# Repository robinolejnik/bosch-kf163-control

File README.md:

# bosch-kf163-control
Replacement PLL/TGA PCB to control Bosch KF83/KF163/KF453/KF165 radios

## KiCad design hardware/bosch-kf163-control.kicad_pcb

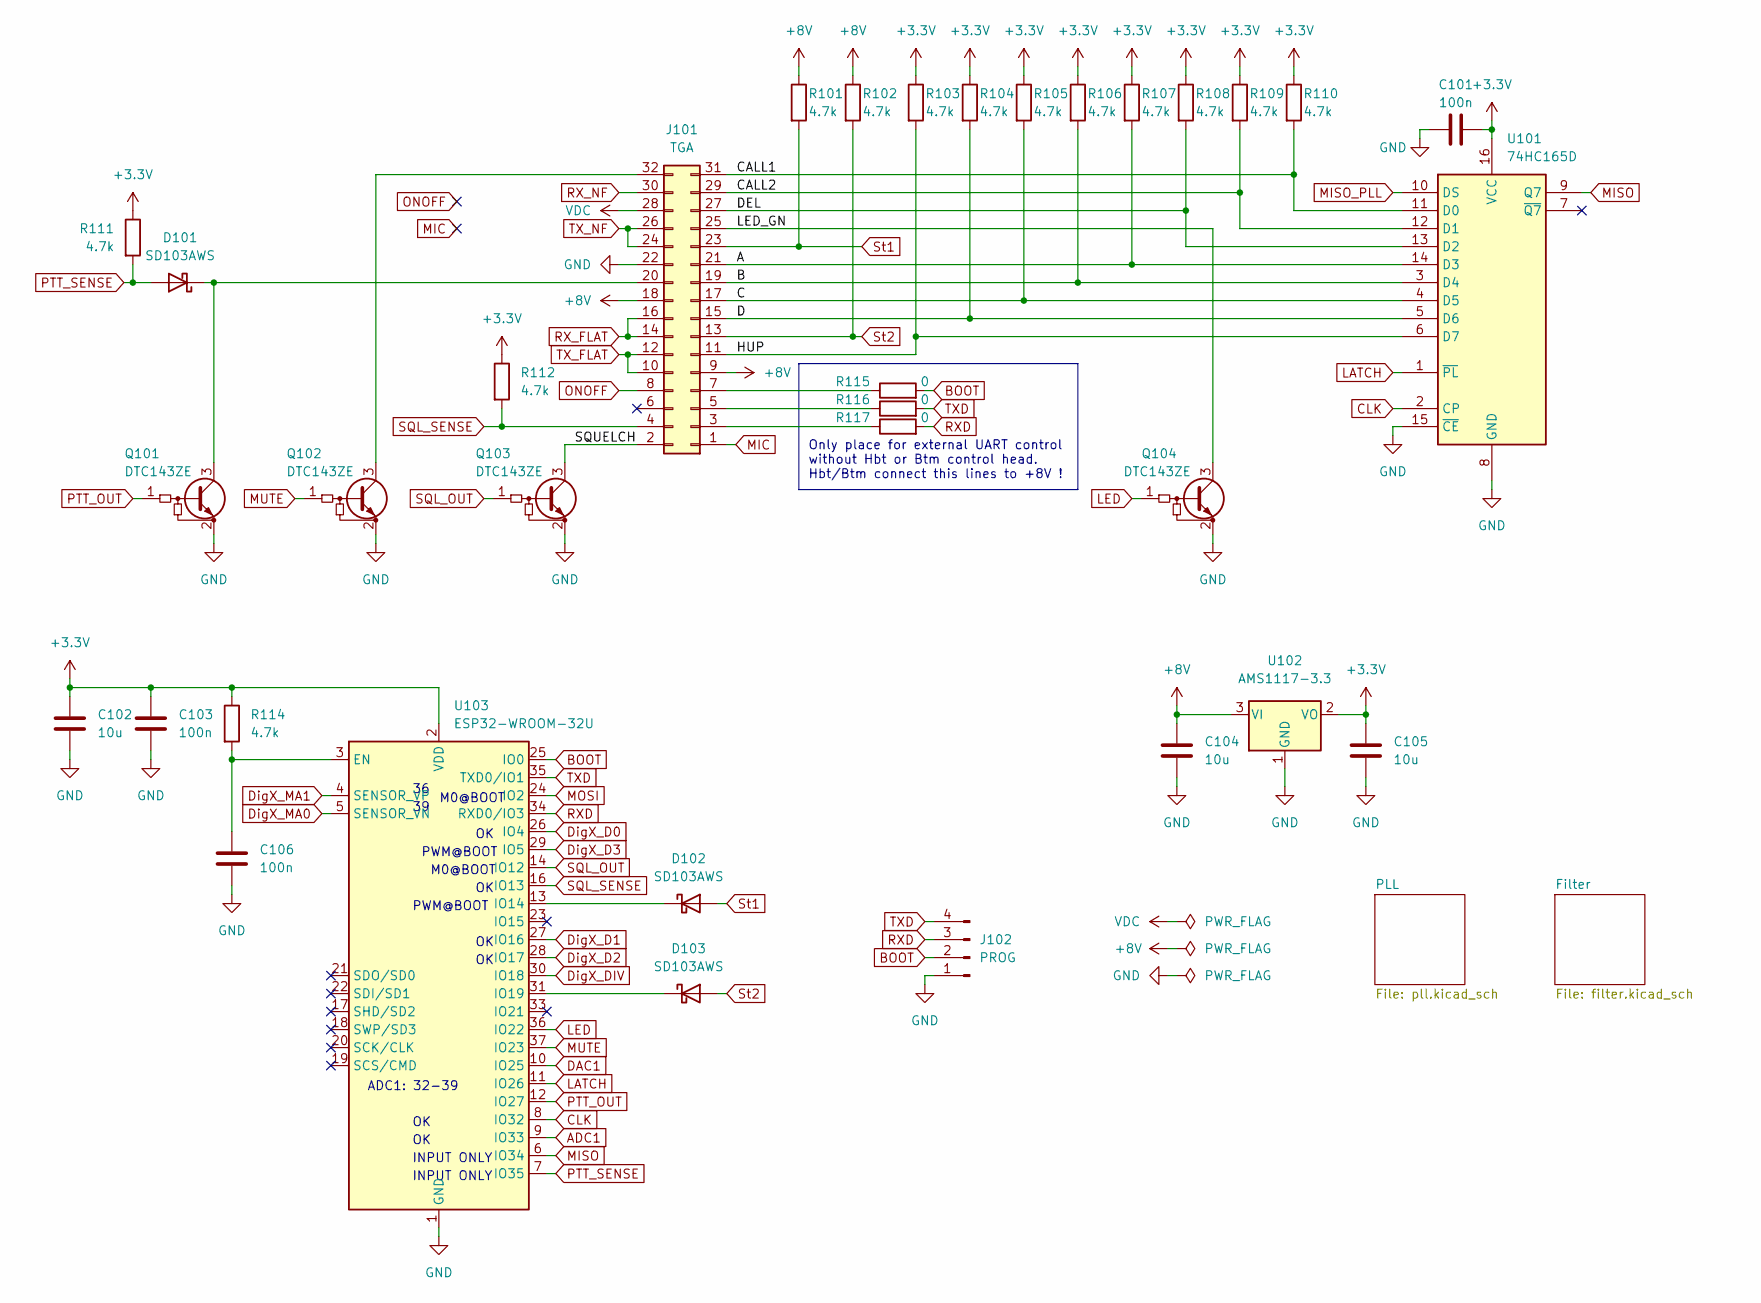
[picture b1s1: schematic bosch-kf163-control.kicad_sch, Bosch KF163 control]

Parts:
C101, C103, C106: 100n; C_0603_1608Metric; LCSC C14663
C102, C104, C105: 10u; C_0603_1608Metric; LCSC C2922482
D101, D102, D103: SD103AWS; D_SOD-323; LCSC C438010
J101: TGA; PinSocket_2x16_P2.54mm_Vertical; LCSC C115248
J102: PROG; PinHeader_1x04_P2.54mm_Vertical
Q101, Q102, Q103, Q104: DTC143ZE; SOT-523; LCSC C248787
R101, R102, R103, R104, R105, R106, R107, R108, R109, R110, R111, R112, R114: 4.7k; R_0603_1608Metric; LCSC C105428
R115, R116, R117: 0; R_0603_1608Metric; LCSC C100044
U101: 74HC165D; SOIC-16_3.9x9.9mm_P1.27mm; LCSC C5613
U102: AMS1117-3.3; SOT-223-3_TabPin2; LCSC C173386
U103: ESP32-WROOM-32U; LCSC C328062

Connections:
+3V3: C101.2, C102.1, C103.1, C105.1, R103.1, R104.1, R105.1, R106.1, R107.1, R108.1, R109.1, R110.1, R111.1, R112.1, R114.1, U101.16 (VCC), U102.2 (VO), U103.2 (VDD); also elsewhere on the board
+8V: C104.1, J101.9, J101.18, R101.1, R102.1, U102.3 (VI)
/A: J101.21, R107.2, U101.14 (D3)
/B: J101.19, R106.2, U101.3 (D4)
/C: J101.17, R105.2, U101.4 (D5)
/CALL1: J101.31, R110.2, U101.11 (D0)
/CALL2: J101.29, R109.2, U101.12 (D1)
/D: J101.15, R104.2, U101.5 (D6)
/DEL: J101.27, R108.2, U101.13 (D2)
/HUP: J101.11, R103.2, U101.6 (D7)
/LED_GN: J101.25, Q104.3 (C)
/SQUELCH: J101.2, Q103.3 (C)
ADC1: U103.9 (IO33); also elsewhere on the board
BOOT: J102.2, R115.2, U103.25 (IO0)
CLK: U101.2 (CP), U103.8 (IO32); also elsewhere on the board
DAC1: U103.10 (IO25); also elsewhere on the board
DigX_D0: U103.26 (IO4); also elsewhere on the board
DigX_D1: U103.27 (IO16); also elsewhere on the board
DigX_D2: U103.28 (IO17); also elsewhere on the board
DigX_D3: U103.29 (IO5); also elsewhere on the board
DigX_DIV: U103.30 (IO18); also elsewhere on the board
DigX_MA0: U103.5 (SENSOR_VN); also elsewhere on the board
DigX_MA1: U103.4 (SENSOR_VP); also elsewhere on the board
GND: C101.1, C102.2, C103.2, C104.2, C105.2, C106.2, J101.22, J102.1, Q101.2 (E), Q102.2 (E), Q103.2 (E), Q104.2 (E), U101.8 (GND), U101.15 (~CE), U102.1 (GND), U103.1 (GND), U103.15 (GND), U103.38 (GND), U103.39 (GND); also elsewhere on the board
LATCH: U101.1 (~PL), U103.11 (IO26); also elsewhere on the board
LED: Q104.1 (B), U103.36 (IO22)
MIC: J101.1
MISO: U101.9 (Q7), U103.6 (IO34)
MISO_PLL: U101.10 (DS); also elsewhere on the board
MOSI: U103.24 (IO2); also elsewhere on the board
MUTE: Q102.1 (B), U103.37 (IO23)
unnamed: C106.1, R114.2, U103.3 (EN)
unnamed: D101.1 (K), J101.20, Q101.3 (C)
unnamed: D102.1 (K), U103.13 (IO14)
unnamed: D103.1 (K), U103.31 (IO19)
unnamed: J101.3, R117.1
unnamed: J101.5, R116.1
unnamed: J101.7, R115.1
unnamed: J101.32, Q102.3 (C)
ONOFF: J101.8
PTT_OUT: Q101.1 (B), U103.12 (IO27)
PTT_SENSE: D101.2 (A), R111.2, U103.7 (IO35)
RXD: J102.3, R117.2, U103.34 (RXD0/IO3)
RX_FLAT: J101.14, J101.16; also elsewhere on the board
RX_NF: J101.30; also elsewhere on the board
SQL_OUT: Q103.1 (B), U103.14 (IO12)
SQL_SENSE: J101.4, R112.2, U103.16 (IO13)
St1: D102.2 (A), J101.23, R101.2
St2: D103.2 (A), J101.13, R102.2
TXD: J102.4, R116.2, U103.35 (TXD0/IO1)
TX_FLAT: J101.10, J101.12; also elsewhere on the board
TX_NF: J101.24, J101.26; also elsewhere on the board
VDC: J101.28

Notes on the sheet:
ADC1: 32-39
M0@BOOT
INPUT ONLY
PWM@BOOT
Only place for external UART control without Hbt or Btm control head. Hbt/Btm connect this lines to +8V !

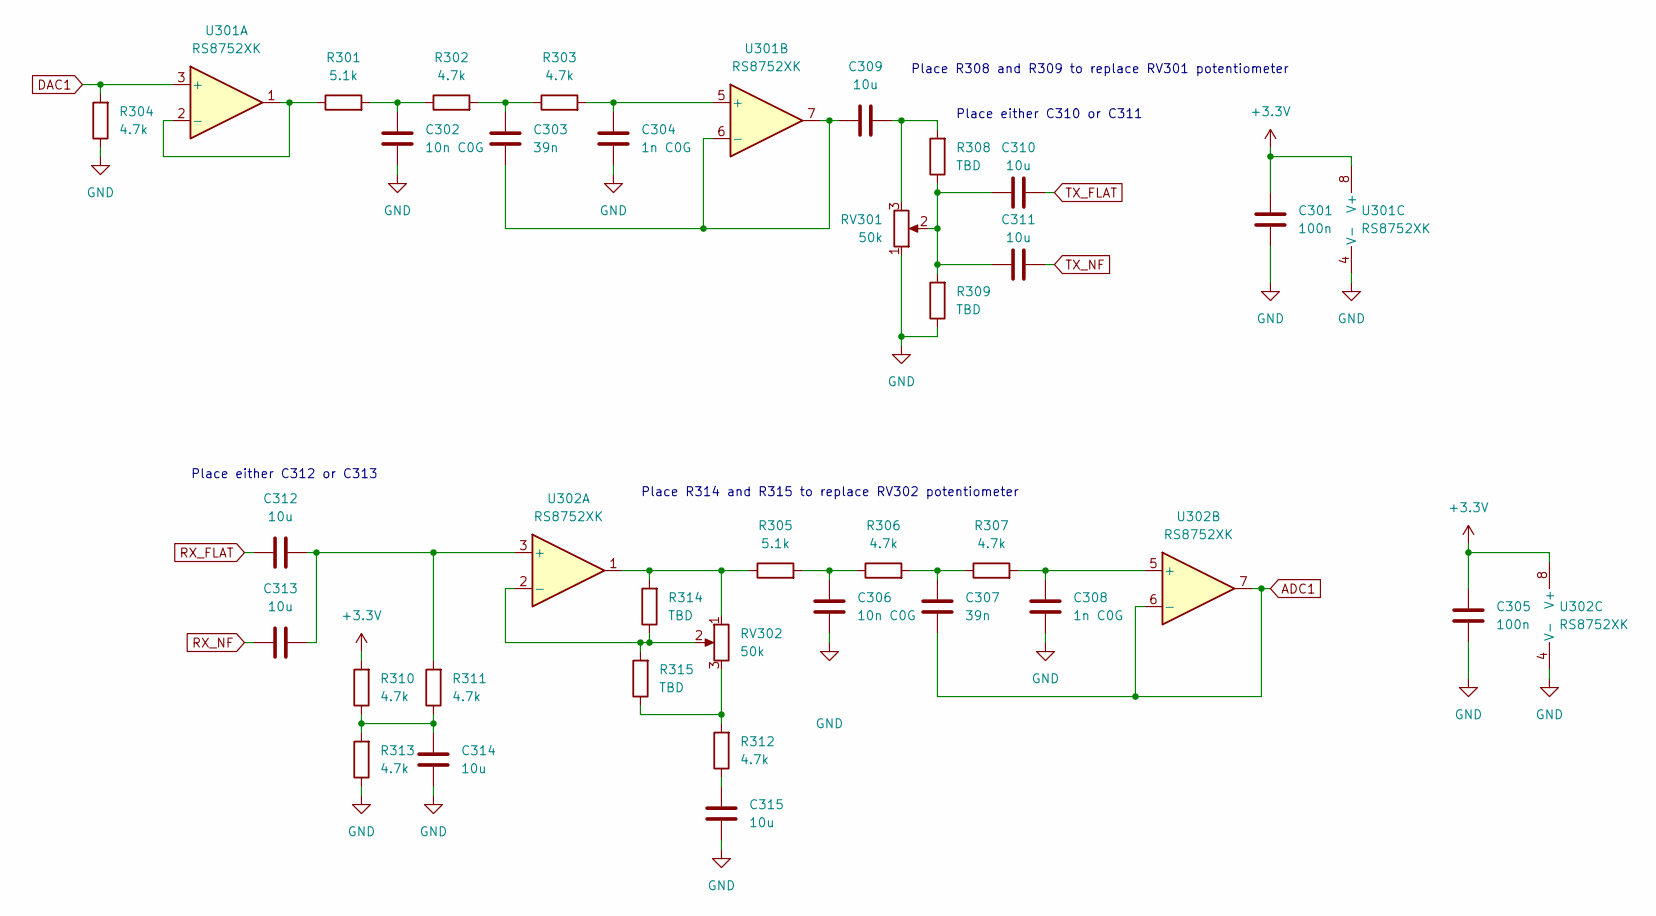
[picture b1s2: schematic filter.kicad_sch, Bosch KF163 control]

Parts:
C301, C305: 100n; C_0603_1608Metric; LCSC C14663
C302, C306: 10n C0G; C_0603_1608Metric; LCSC C389113
C303, C307: 39n; C_0603_1608Metric; LCSC C107091
C304, C308: 1n C0G; C_0603_1608Metric; LCSC C106246
C309, C310, C311, C312, C313, C314, C315: 10u; C_0603_1608Metric; LCSC C2922482
R301, R305: 5.1k; R_0603_1608Metric; LCSC C23186
R302, R303, R304, R306, R307, R310, R311, R312, R313: 4.7k; R_0603_1608Metric; LCSC C105428
R308, R309, R314, R315: TBD; R_0603_1608Metric
RV301, RV302: 50k; Potentiometer_Bourns_TC33X_Vertical; LCSC C145161
U301, U302: RS8752XK; SOIC-8_3.9x4.9mm_P1.27mm; LCSC C236994

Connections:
+3V3: C301.1, C305.1, R310.2, U301.8 (V+), U302.8 (V+); also elsewhere on the board
ADC1: C307.2, U302.6 (-), U302.7; also elsewhere on the board
DAC1: R304.2, U301.3 (+); also elsewhere on the board
GND: C301.2, C302.2, C304.2, C305.2, C306.2, C308.2, C314.2, C315.2, R304.1, R309.1, R313.1, RV301.1, U301.4 (V-), U302.4 (V-); also elsewhere on the board
unnamed: C302.1, R301.2, R302.1
unnamed: C303.1, R302.2, R303.1
unnamed: C303.2, C309.1, U301.6 (-), U301.7
unnamed: C304.1, R303.2, U301.5 (+)
unnamed: C306.1, R305.2, R306.1
unnamed: C307.1, R306.2, R307.1
unnamed: C308.1, R307.2, U302.5 (+)
unnamed: C309.2, R308.2, RV301.3
unnamed: C310.1, C311.1, R308.1, R309.2, RV301.2
unnamed: C312.2, C313.2, R311.2, U302.3 (+)
unnamed: C314.1, R310.1, R311.1, R313.2
unnamed: C315.1, R312.1
unnamed: R301.1, U301.1, U301.2 (-)
unnamed: R305.1, R314.2, RV302.1, U302.1
unnamed: R312.2, R315.1, RV302.3
unnamed: R314.1, R315.2, RV302.2, U302.2 (-)
RX_FLAT: C312.1; also elsewhere on the board
RX_NF: C313.1; also elsewhere on the board
TX_FLAT: C310.2; also elsewhere on the board
TX_NF: C311.2; also elsewhere on the board

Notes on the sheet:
Place R308 and R309 to replace RV301 potentiometer
Place either C310 or C311
Place R314 and R315 to replace RV302 potentiometer
Place either C312 or C313

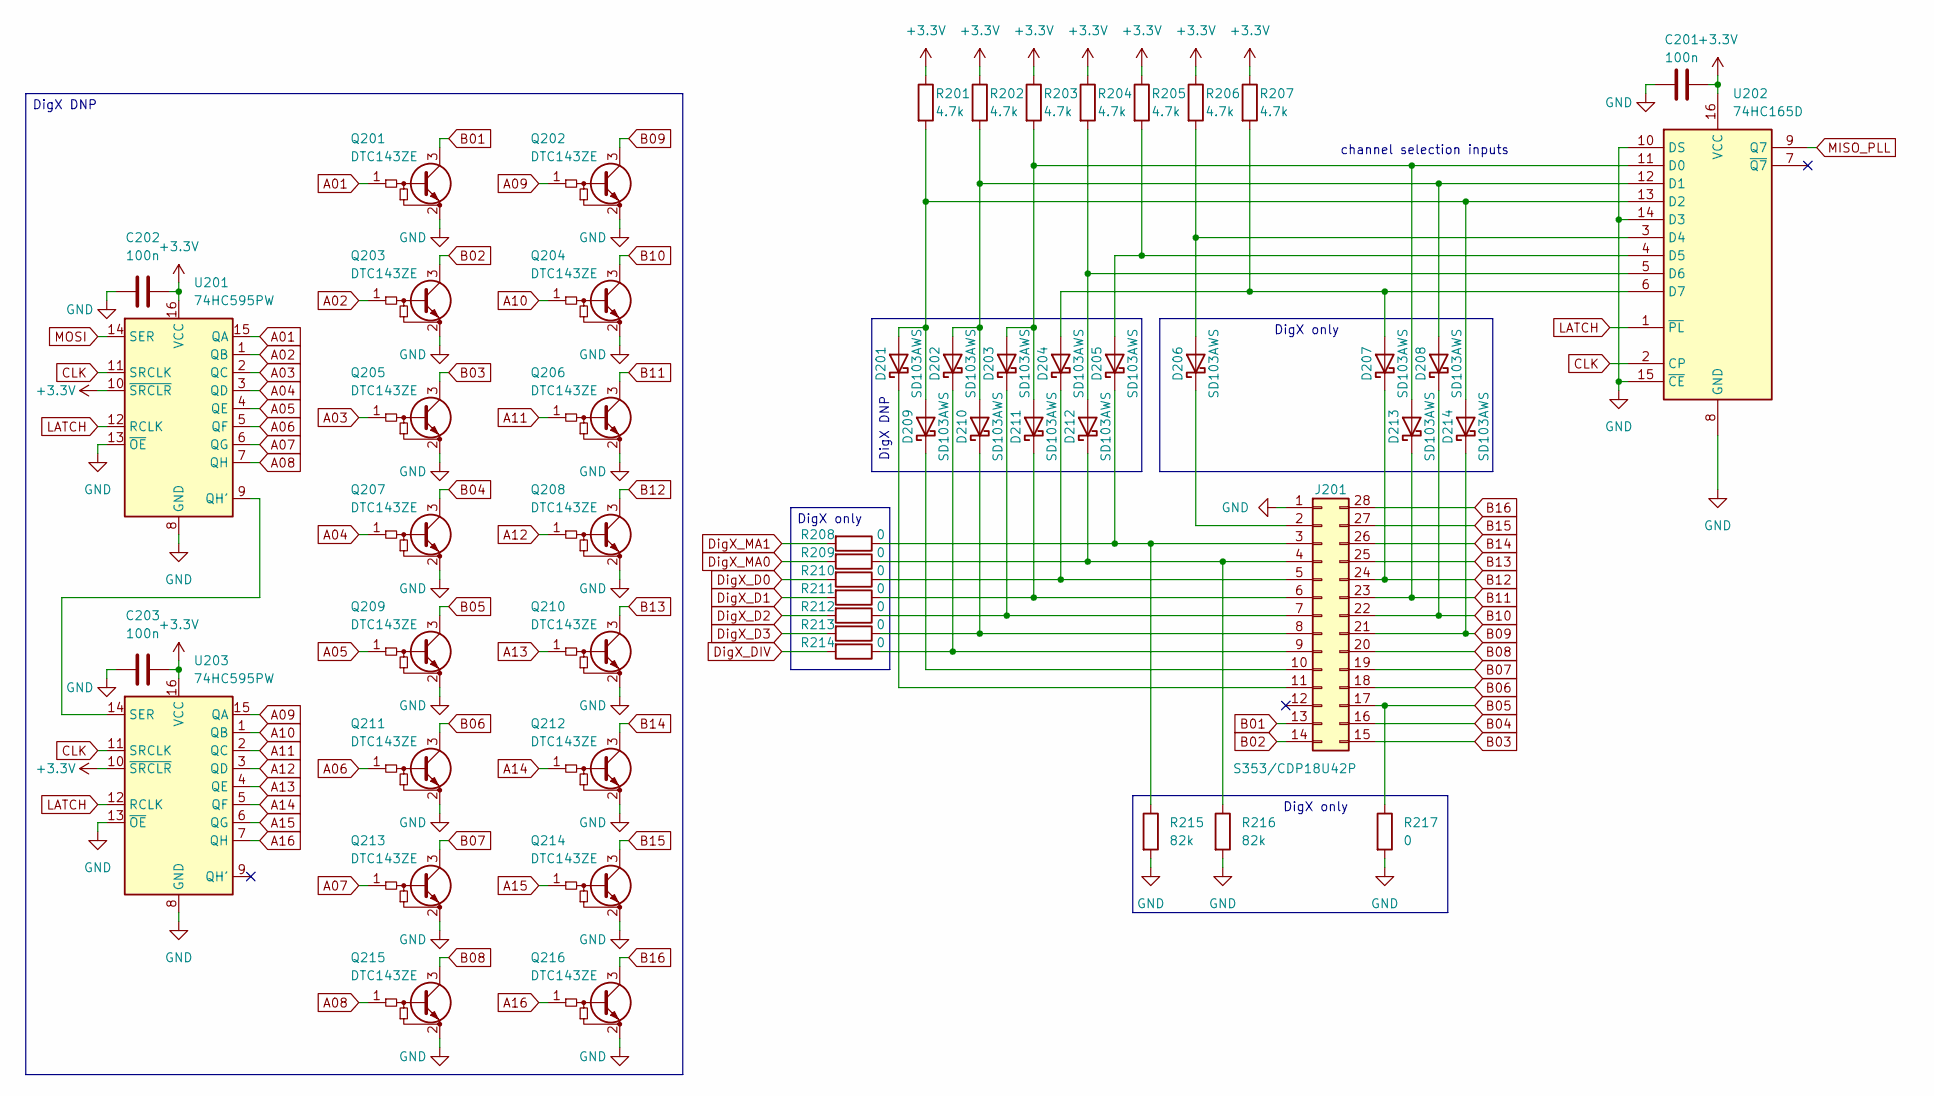
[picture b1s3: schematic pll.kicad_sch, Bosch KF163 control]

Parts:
C201, C202, C203: 100n; C_0603_1608Metric; LCSC C14663
D201, D202, D203, D204, D205, D206, D207, D208, D209, D210, D211, D212, D213, D214: SD103AWS; D_SOD-323; LCSC C438010
J201: S353/CDP18U42P; DIP-28_W15.24mm_Socket_LongPads; LCSC C510960
Q201, Q202, Q203, Q204, Q205, Q206, Q207, Q208, Q209, Q210, Q211, Q212, Q213, Q214, Q215, Q216: DTC143ZE; SOT-523; LCSC C248787
R201, R202, R203, R204, R205, R206, R207: 4.7k; R_0603_1608Metric; LCSC C105428
R208, R209, R210, R211, R212, R213, R214, R217: 0; R_0603_1608Metric; LCSC C100044
R215, R216: 82k; R_0603_1608Metric; LCSC C103831
U201, U203: 74HC595PW; TSSOP-16_4.4x5mm_P0.65mm; LCSC C5948
U202: 74HC165D; SOIC-16_3.9x9.9mm_P1.27mm; LCSC C5613

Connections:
+3V3: C201.2, C202.2, C203.2, R201.1, R202.1, R203.1, R204.1, R205.1, R206.1, R207.1, U201.10 (~SRCLR), U201.16 (VCC), U202.16 (VCC), U203.10 (~SRCLR), U203.16 (VCC); also elsewhere on the board
A01: Q201.1 (B), U201.15 (QA)
A02: Q203.1 (B), U201.1 (QB)
A03: Q205.1 (B), U201.2 (QC)
A04: Q207.1 (B), U201.3 (QD)
A05: Q209.1 (B), U201.4 (QE)
A06: Q211.1 (B), U201.5 (QF)
A07: Q213.1 (B), U201.6 (QG)
A08: Q215.1 (B), U201.7 (QH)
A09: Q202.1 (B), U203.15 (QA)
A10: Q204.1 (B), U203.1 (QB)
A11: Q206.1 (B), U203.2 (QC)
A12: Q208.1 (B), U203.3 (QD)
A13: Q210.1 (B), U203.4 (QE)
A14: Q212.1 (B), U203.5 (QF)
A15: Q214.1 (B), U203.6 (QG)
A16: Q216.1 (B), U203.7 (QH)
B01: J201.13, Q201.3 (C)
B02: J201.14, Q203.3 (C)
B03: J201.15, Q205.3 (C)
B04: J201.16, Q207.3 (C)
B05: J201.17, Q209.3 (C), R217.1
B06: J201.18, Q211.3 (C)
B07: J201.19, Q213.3 (C)
B08: J201.20, Q215.3 (C)
B09: D214.1 (K), J201.21, Q202.3 (C)
B10: D208.1 (K), J201.22, Q204.3 (C)
B11: D213.1 (K), J201.23, Q206.3 (C)
B12: D207.1 (K), J201.24, Q208.3 (C)
B13: J201.25, Q210.3 (C)
B14: J201.26, Q212.3 (C)
B15: J201.27, Q214.3 (C)
B16: J201.28, Q216.3 (C)
CLK: U201.11 (SRCLK), U202.2 (CP), U203.11 (SRCLK); also elsewhere on the board
DigX_D0: R210.2; also elsewhere on the board
DigX_D1: R211.2; also elsewhere on the board
DigX_D2: R212.2; also elsewhere on the board
DigX_D3: R213.2; also elsewhere on the board
DigX_DIV: R214.2; also elsewhere on the board
DigX_MA0: R209.2; also elsewhere on the board
DigX_MA1: R208.2; also elsewhere on the board
GND: C201.1, C202.1, C203.1, J201.1, Q201.2 (E), Q202.2 (E), Q203.2 (E), Q204.2 (E), Q205.2 (E), Q206.2 (E), Q207.2 (E), Q208.2 (E), Q209.2 (E), Q210.2 (E), Q211.2 (E), Q212.2 (E), Q213.2 (E), Q214.2 (E), Q215.2 (E), Q216.2 (E), R215.2, R216.2, R217.2, U201.8 (GND), U201.13 (~OE), U202.8 (GND), U202.10 (DS), U202.14 (D3), U202.15 (~CE), U203.8 (GND), U203.13 (~OE); also elsewhere on the board
LATCH: U201.12 (RCLK), U202.1 (~PL), U203.12 (RCLK); also elsewhere on the board
MISO_PLL: U202.9 (Q7); also elsewhere on the board
MOSI: U201.14 (SER); also elsewhere on the board
unnamed: D201.1 (K), J201.11
unnamed: D201.2 (A), D209.2 (A), D214.2 (A), R201.2, U202.13 (D2)
unnamed: D202.1 (K), J201.9, R214.1
unnamed: D202.2 (A), D208.2 (A), D210.2 (A), R202.2, U202.12 (D1)
unnamed: D203.1 (K), J201.7, R212.1
unnamed: D203.2 (A), D211.2 (A), D213.2 (A), R203.2, U202.11 (D0)
unnamed: D204.1 (K), J201.5, R210.1
unnamed: D204.2 (A), D207.2 (A), R207.2, U202.6 (D7)
unnamed: D205.1 (K), J201.3, R208.1, R215.1
unnamed: D205.2 (A), R205.2, U202.4 (D5)
unnamed: D206.1 (K), J201.2
unnamed: D206.2 (A), R206.2, U202.3 (D4)
unnamed: D209.1 (K), J201.10
unnamed: D210.1 (K), J201.8, R213.1
unnamed: D211.1 (K), J201.6, R211.1
unnamed: D212.1 (K), J201.4, R209.1, R216.1
unnamed: D212.2 (A), R204.2, U202.5 (D6)
unnamed: U201.9 (QH'), U203.14 (SER)

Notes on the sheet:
DigX only
DigX DNP
channel selection inputs

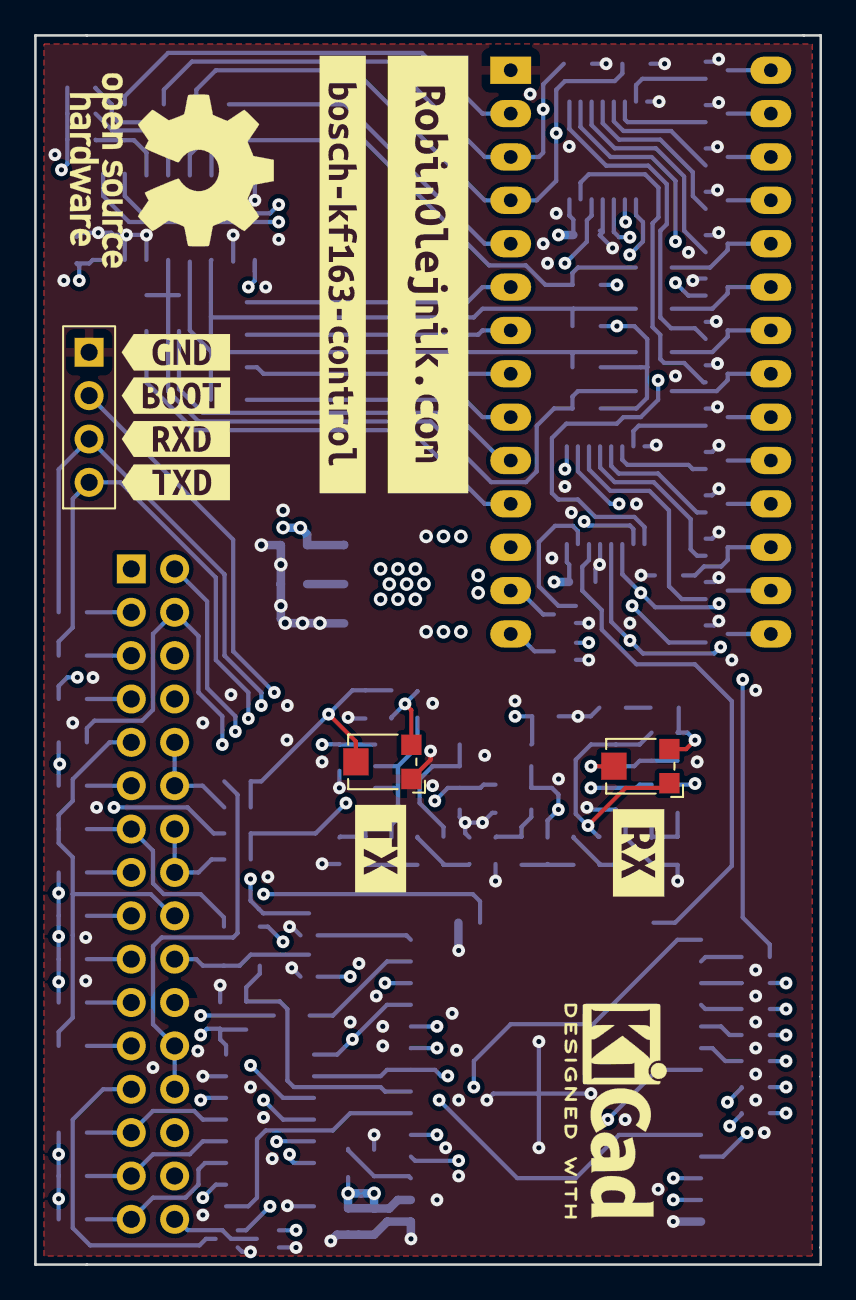
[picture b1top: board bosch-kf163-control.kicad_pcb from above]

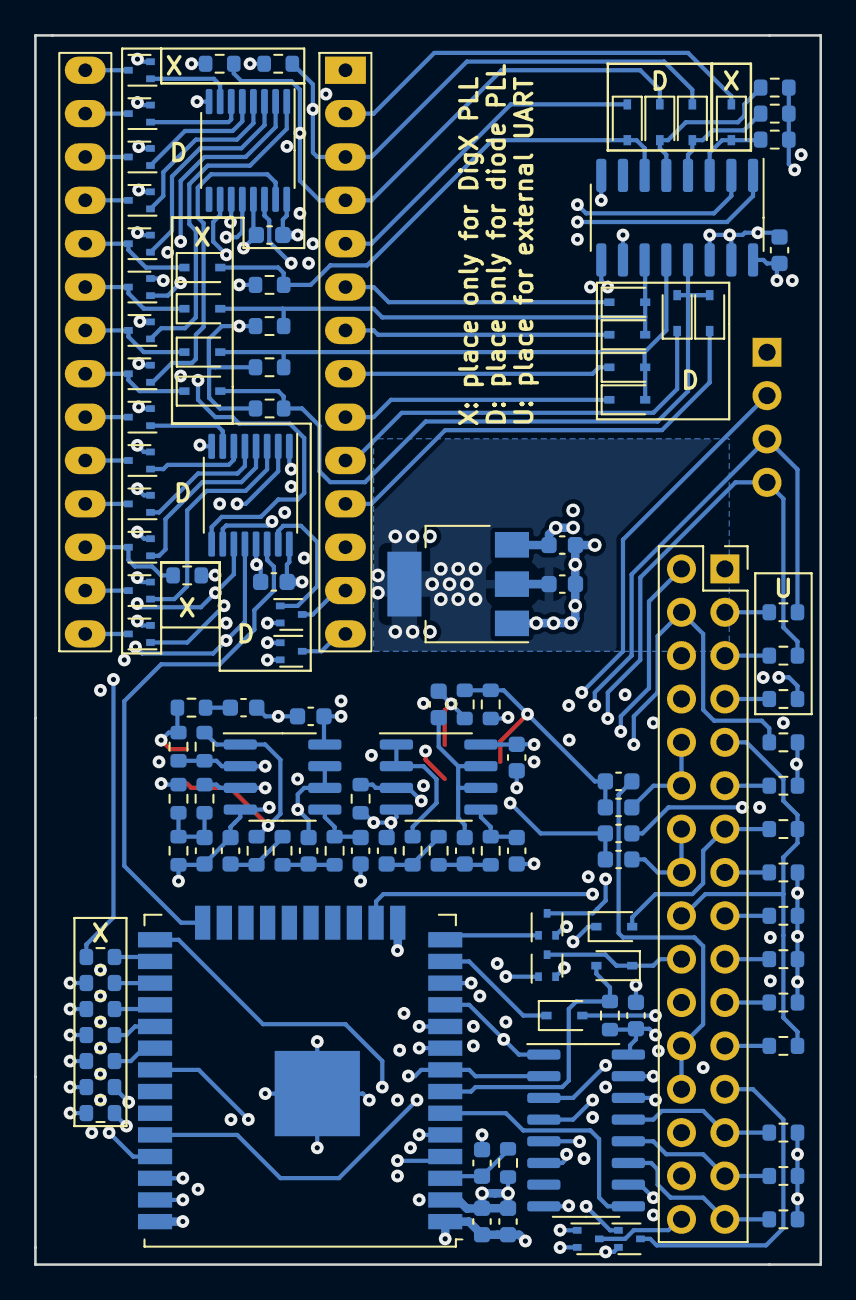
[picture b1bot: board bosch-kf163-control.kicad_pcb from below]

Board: 4 copper layers, 46.0 x 72.0 mm, 130 parts (119 on the bottom side), 116 nets.

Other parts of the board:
kibuzzard-61EB12C7: G***; kibuzzard-61EB12C7
kibuzzard-61EB12DB: G***; kibuzzard-61EB12DB
kibuzzard-61EB14A1: G***; kibuzzard-61EB14A1
kibuzzard-61EB122B: G***; kibuzzard-61EB122B
kibuzzard-61EB123A: G***; kibuzzard-61EB123A
kibuzzard-61EB1225: G***; kibuzzard-61EB1225
kibuzzard-61EB1233: G***; kibuzzard-61EB1233
kibuzzard-61EB1504: G***; kibuzzard-61EB1504

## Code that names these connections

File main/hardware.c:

#include "hardware.h"

void gpio_init(void) {
    gpio_set_direction(GPIO_PTT_SENSE, GPIO_MODE_INPUT);
    gpio_set_direction(GPIO_PTT_OUT, GPIO_MODE_OUTPUT);

    gpio_set_direction(GPIO_SQL_SENSE, GPIO_MODE_INPUT);
    gpio_set_direction(GPIO_SQL_OUT, GPIO_MODE_OUTPUT);

    gpio_set_direction(GPIO_MUTE, GPIO_MODE_OUTPUT);
    gpio_set_direction(GPIO_LED, GPIO_MODE_OUTPUT);

    gpio_set_direction(GPIO_DIGX_MA0, GPIO_MODE_INPUT);
    gpio_set_direction(GPIO_DIGX_MA1, GPIO_MODE_INPUT);
    gpio_set_direction(GPIO_DIGX_D0, GPIO_MODE_OUTPUT);
    gpio_set_direction(GPIO_DIGX_D1, GPIO_MODE_OUTPUT);
    gpio_set_direction(GPIO_DIGX_D2, GPIO_MODE_OUTPUT);
    gpio_set_direction(GPIO_DIGX_D3, GPIO_MODE_OUTPUT);
    gpio_set_direction(GPIO_DIGX_DIV, GPIO_MODE_OUTPUT);
}

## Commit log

2022-01-08 initial pll circuit
2022-01-11 Initial TGA-connector, ESP32 and NF-filter circuit.
2022-01-14 schematic/pcb update
2022-01-20 Finished schematic (BOM consolidation, LCSC part numbers) + sheet comments
2022-01-20 renamed project to bosch-kf163-control
2022-01-20 sheet comments, schematic variants, removed txd resistor
2022-01-21 silkscreen symbols and text, various schematic/pcb updates
2022-01-21 Added pdf schematic and pcb gerber files
2022-04-27 Moved KiCad files to hardware folder.
2022-04-27 Added ESP32 firmware frame
2022-04-29 initial KF163 diode pll code
2022-04-30 set output shift register
2023-06-04 Cleaned up project
2023-06-04 Shift register signal generation, PLL code update
2023-06-04 Added GitHub Actions configuration
2023-06-04 Updated vscode settings
2023-06-04 Updated GitHub Actions checkout step
2023-06-05 Basic trx functionality
2023-06-05 Read from shift registers, use call1 button as PTT

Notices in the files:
bosch-kf163-control.kicad_sch:
License: MIT
